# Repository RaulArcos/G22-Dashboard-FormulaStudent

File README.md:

# G22-Dashboard-FormulaStudent
DashBoard project with ATMEGA 328 using CAN BUS to communicate with Link G4+ Storm ECU.

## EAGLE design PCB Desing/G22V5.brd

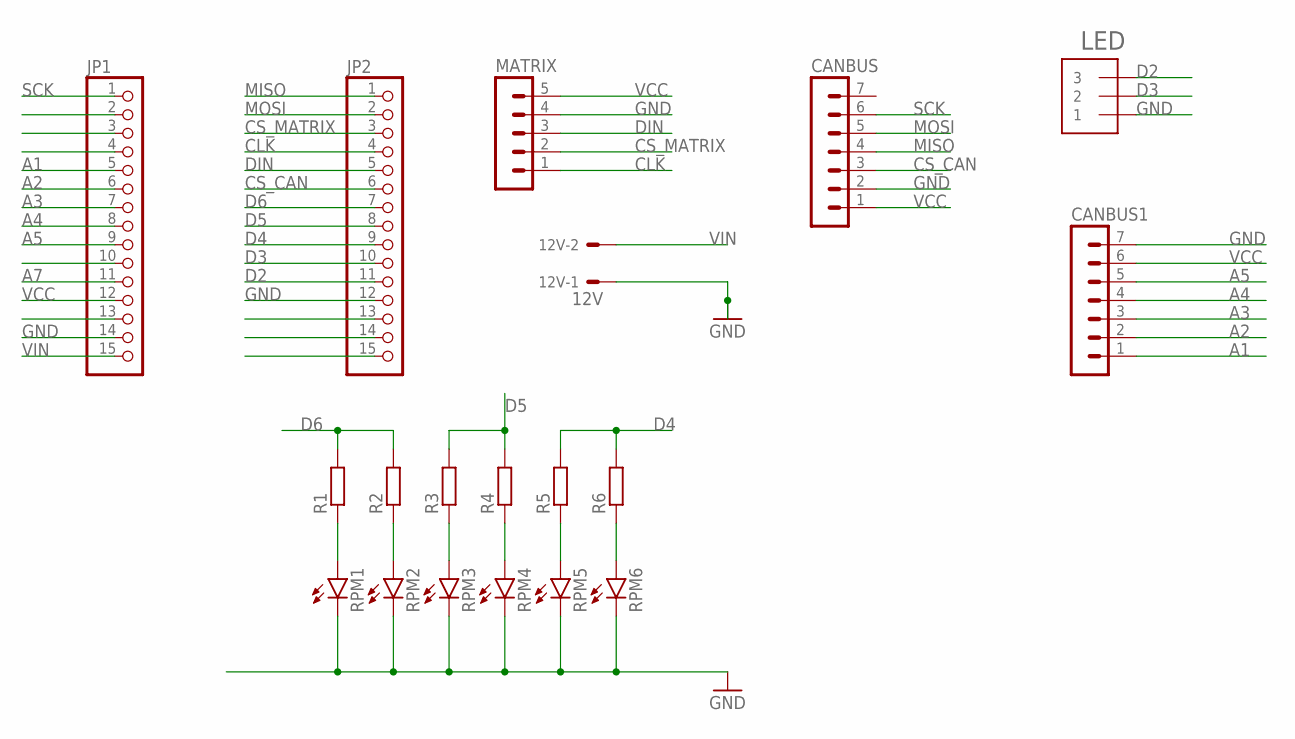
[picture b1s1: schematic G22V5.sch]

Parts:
12V: 12V; 22-23-2021
CANBUS, CANBUS1: MA07-1
JP1, JP2: PINHD-1X15; 1X15
LED: JST_ZH_3
MATRIX: MA05-1
R1, R2, R3, R4, R5, R6: R-EU_M0805; M0805
RPM1, RPM2, RPM3, RPM4, RPM5, RPM6: LED5MM

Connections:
A1: CANBUS1.1, JP1.5
A2: CANBUS1.2, JP1.6
A3: CANBUS1.3, JP1.7
A4: CANBUS1.4, JP1.8
A5: CANBUS1.5, JP1.9
A7: JP1.11
CLK: JP2.4, MATRIX.1
CS_CAN: CANBUS.3, JP2.6
CS_MATRIX: JP2.3, MATRIX.2
D2: JP2.11, LED.P$3 (3)
D3: JP2.10, LED.P$2 (2)
D4: JP2.9, R5.2, R6.2
D5: JP2.8, R3.2, R4.2
D6: JP2.7, R1.2, R2.2
DIN: JP2.5, MATRIX.3
GND: 12V.1, CANBUS.2, CANBUS1.7, JP1.14, JP2.12, LED.P$1 (1), MATRIX.4, RPM1.K (C), RPM2.K (C), RPM3.K (C), RPM4.K (C), RPM5.K (C), RPM6.K (C)
MISO: CANBUS.4, JP2.1
MOSI: CANBUS.5, JP2.2
unnamed: R1.1, RPM1.A
unnamed: R2.1, RPM2.A
unnamed: R3.1, RPM3.A
unnamed: R4.1, RPM4.A
unnamed: R5.1, RPM5.A
unnamed: R6.1, RPM6.A
SCK: CANBUS.6, JP1.1
VCC: CANBUS.1, CANBUS1.6, JP1.12, MATRIX.5
VIN: 12V.2, JP1.15

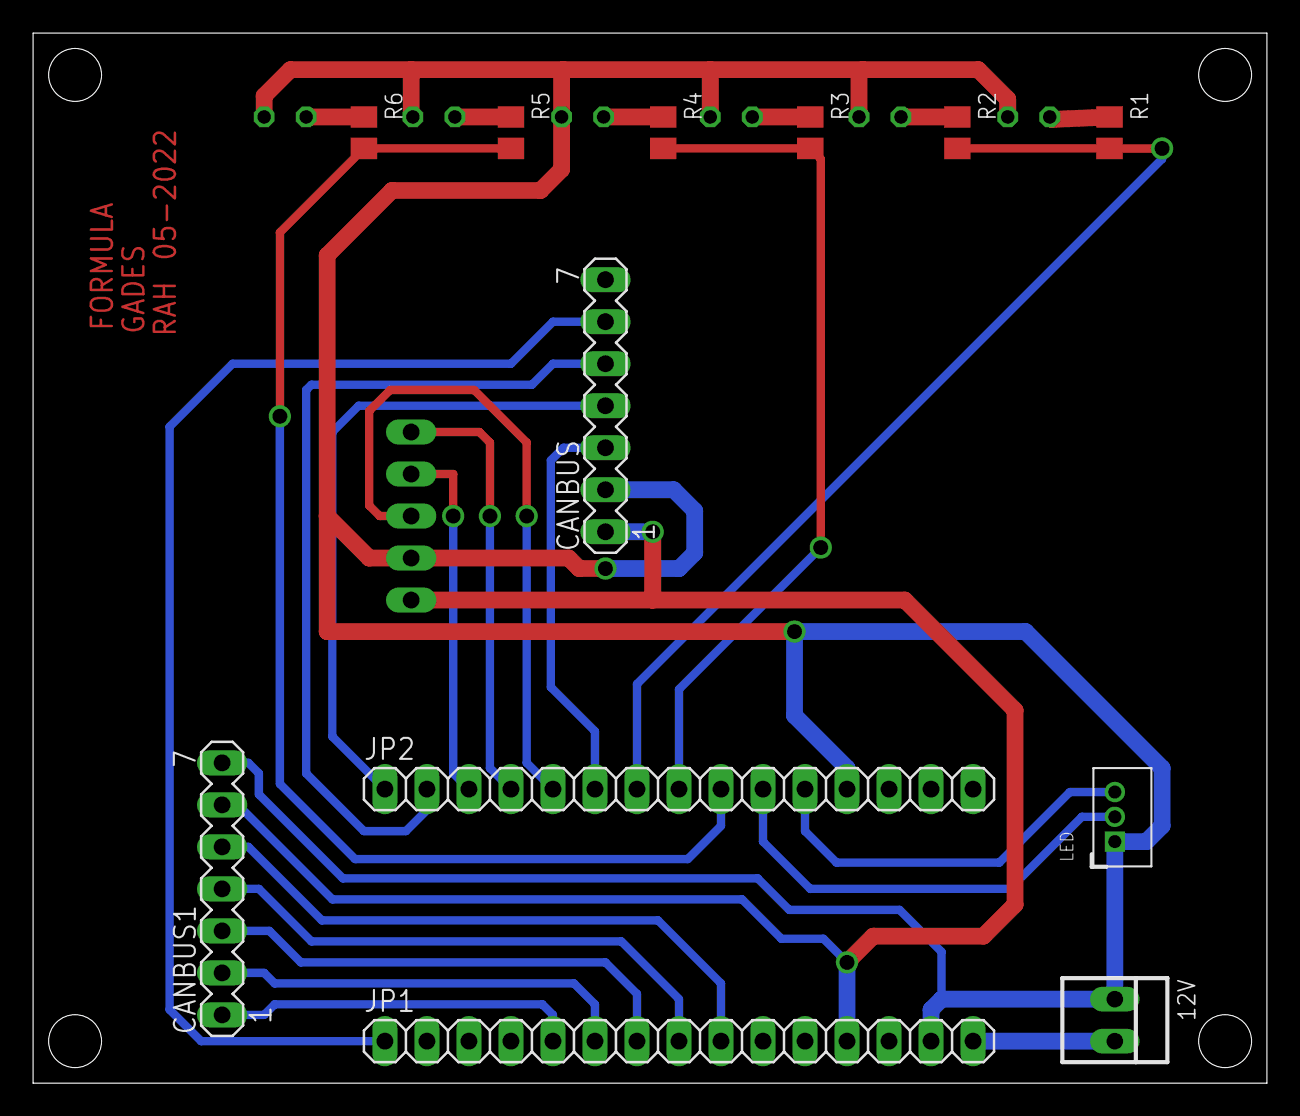
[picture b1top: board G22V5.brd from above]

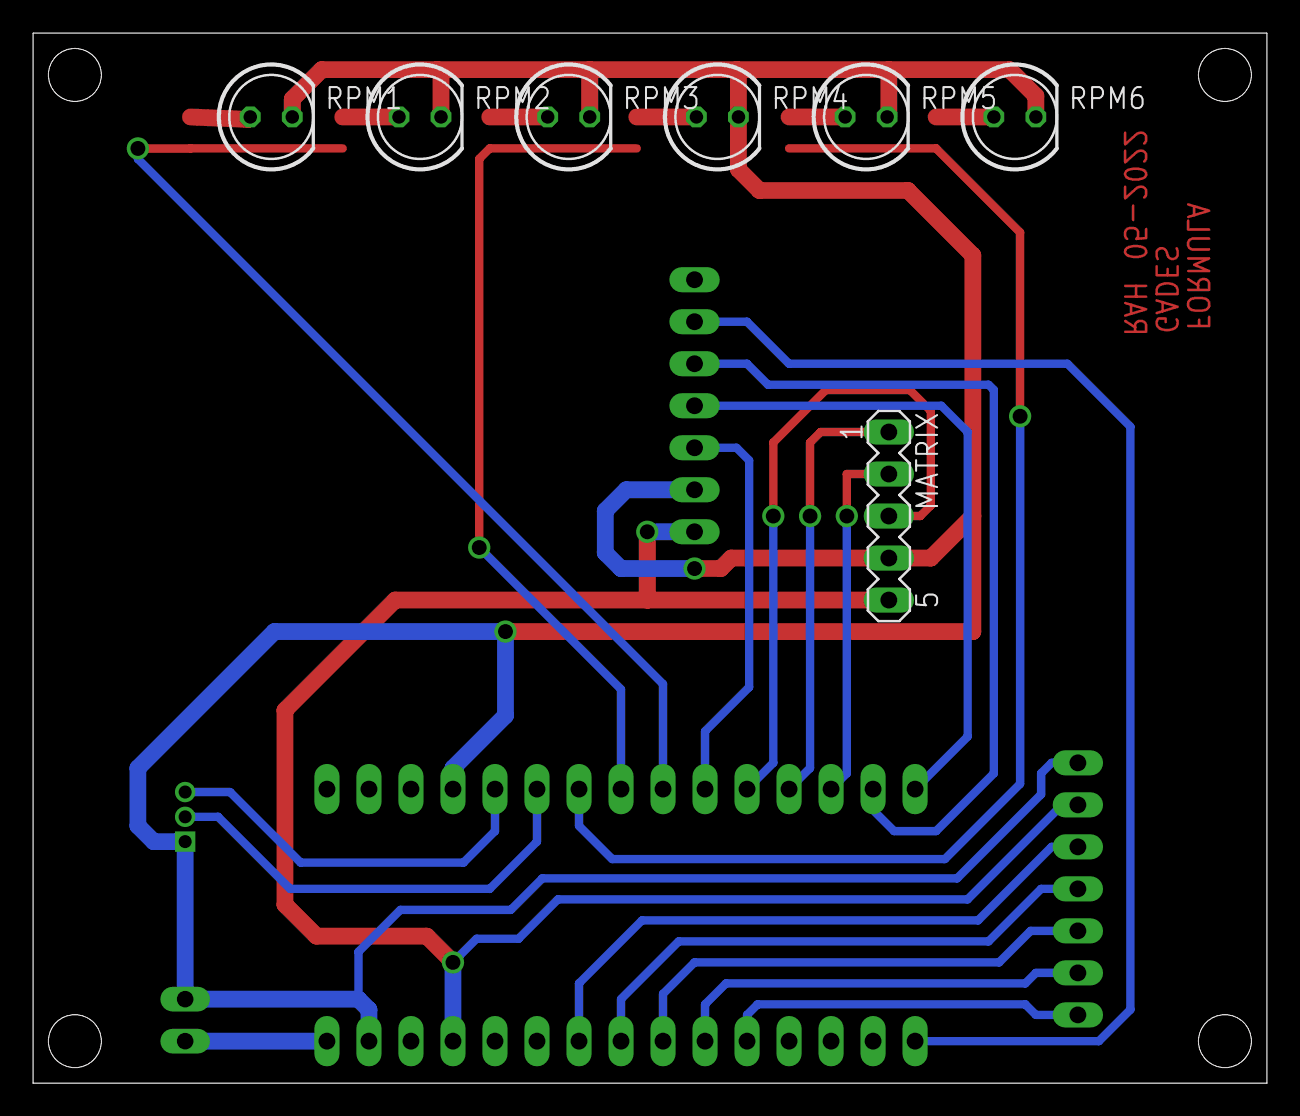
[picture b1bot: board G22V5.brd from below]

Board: 8 copper layers, 74.6 x 63.5 mm, 19 parts (7 on the bottom side), 26 nets.

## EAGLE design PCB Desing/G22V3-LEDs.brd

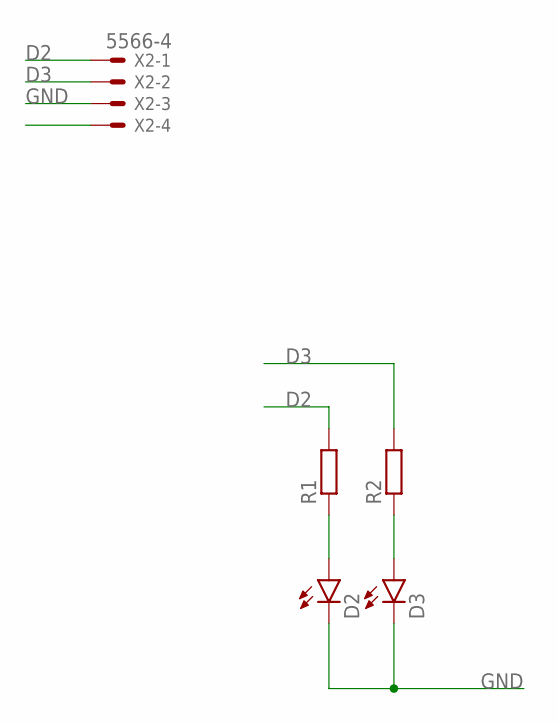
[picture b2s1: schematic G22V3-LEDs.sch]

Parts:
D2, D3: LED5MM
R1, R2: R-EU_0204/7; 0204/7
X2: 5566-4

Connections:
D2: R1.2, X2.1
D3: R2.2, X2.2
GND: D2.K (C), D3.K (C), X2.3
unnamed: D2.A, R1.1
unnamed: D3.A, R2.1

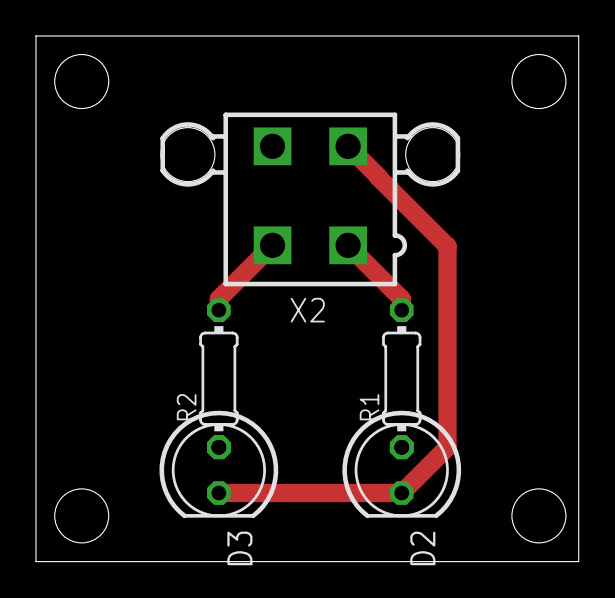
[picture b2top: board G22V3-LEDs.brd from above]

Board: 2 copper layers, 30.1 x 29.2 mm, 5 parts (0 on the bottom side), 5 nets.

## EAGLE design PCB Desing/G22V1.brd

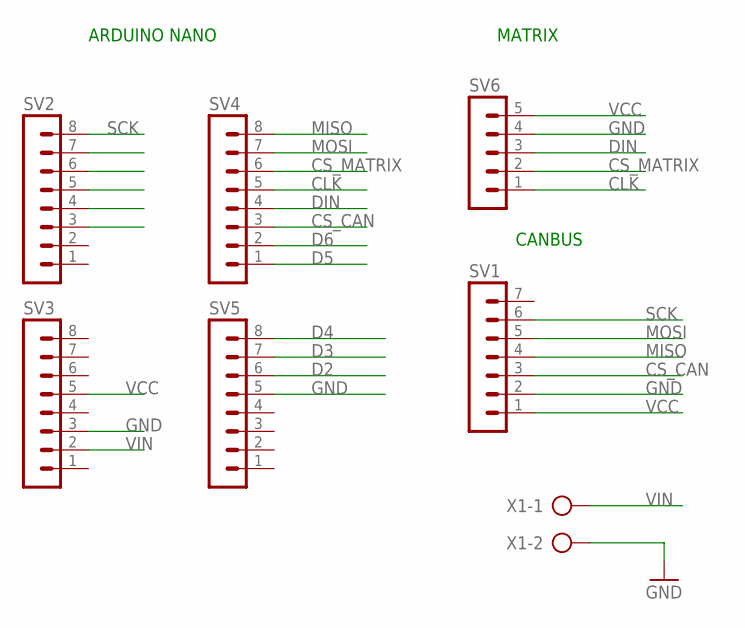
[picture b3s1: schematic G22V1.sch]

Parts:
SV1: MA07-1
SV2, SV3, SV4, SV5: MA08-1
SV6: MA05-1
X1: AK300/2

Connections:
CLK: SV4.5, SV6.1
CS_CAN: SV1.3, SV4.3
CS_MATRIX: SV4.6, SV6.2
D2: SV5.6
D3: SV5.7
D4: SV5.8
D5: SV4.1
D6: SV4.2
DIN: SV4.4, SV6.3
GND: SV1.2, SV3.3, SV5.5, SV6.4, X1.2
MISO: SV1.4, SV4.8
MOSI: SV1.5, SV4.7
SCK: SV1.6, SV2.8
VCC: SV1.1, SV3.5, SV6.5
VIN: SV3.2, X1.1

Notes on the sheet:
ARDUINO NANO
MATRIX
CANBUS

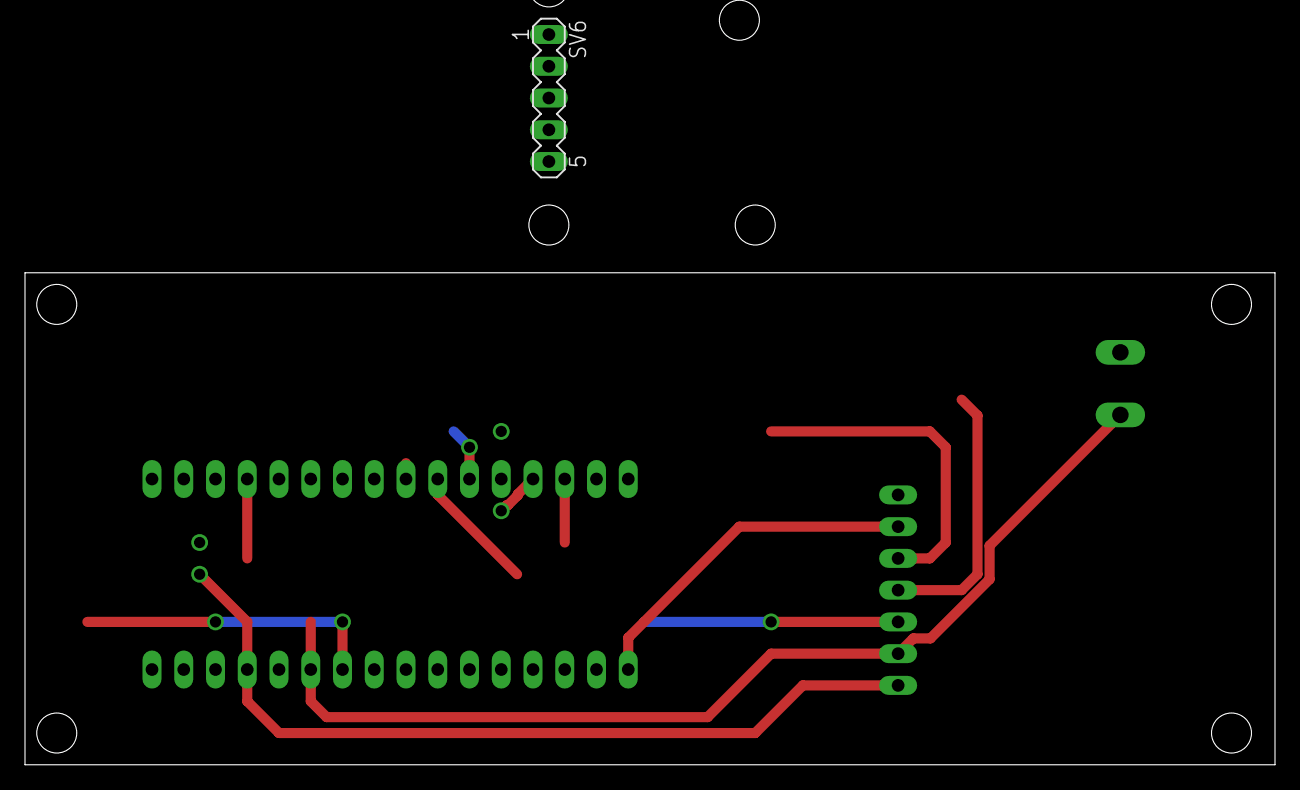
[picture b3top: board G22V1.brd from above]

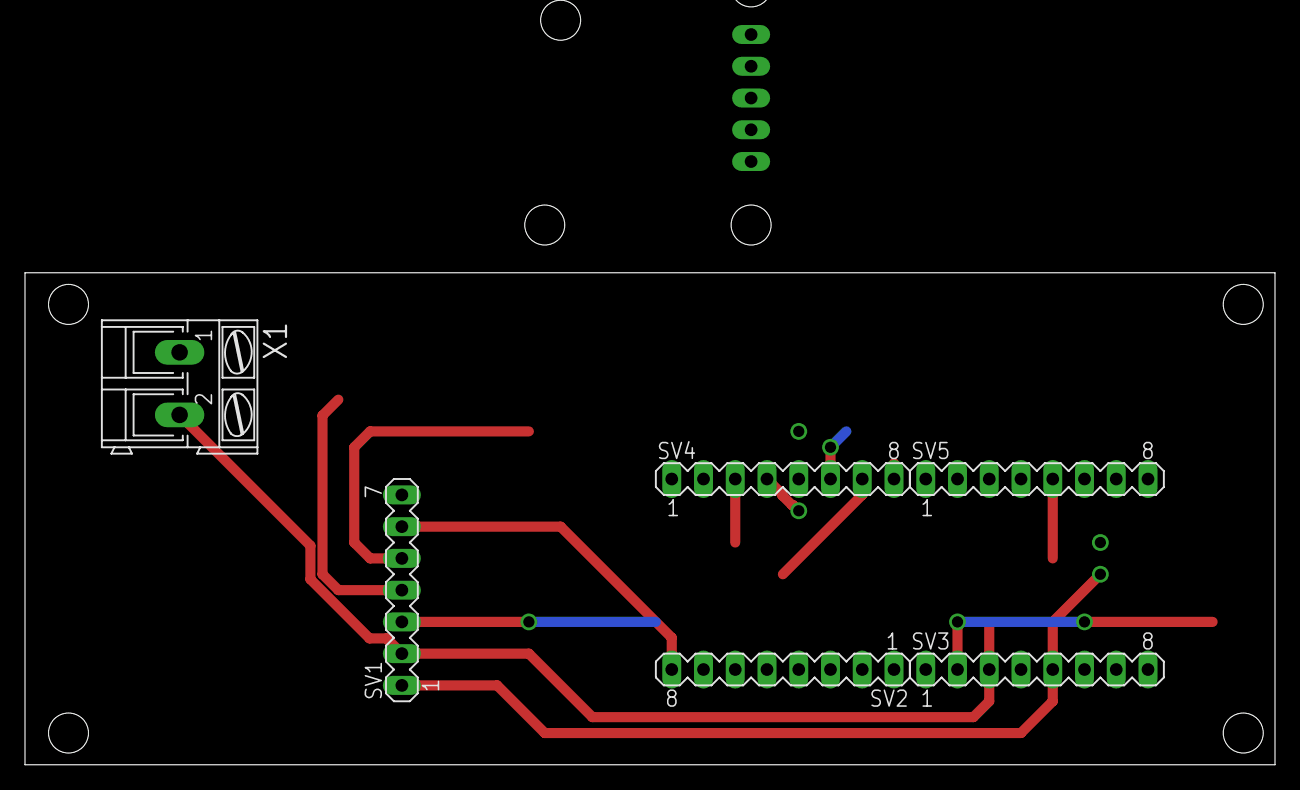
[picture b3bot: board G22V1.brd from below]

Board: 2 copper layers, 100.0 x 39.4 mm, 7 parts (6 on the bottom side), 10 nets.

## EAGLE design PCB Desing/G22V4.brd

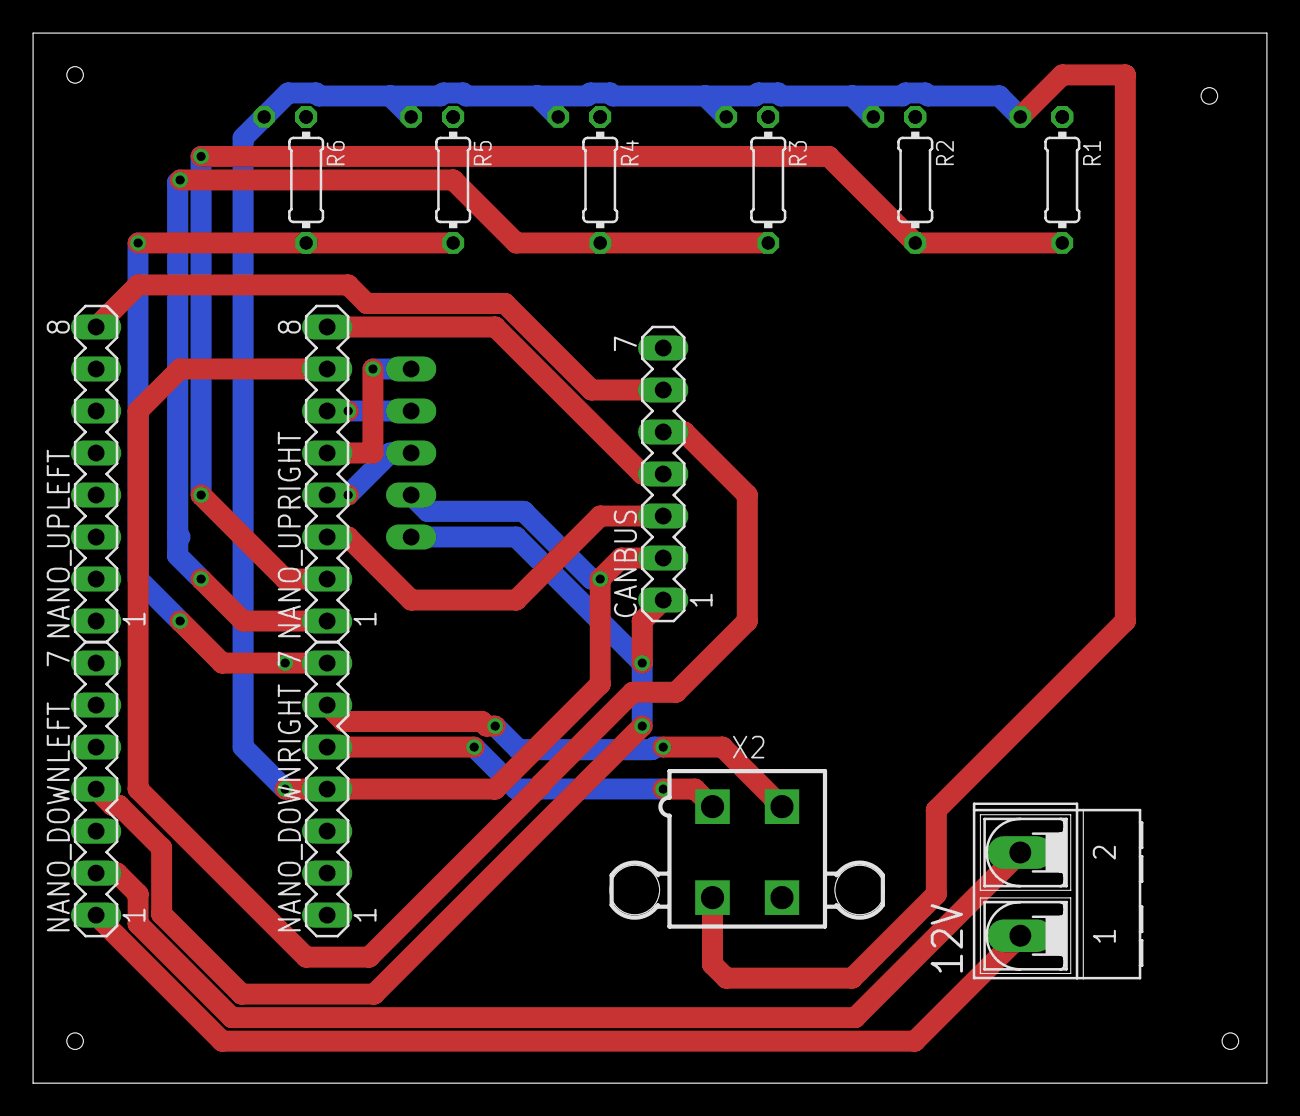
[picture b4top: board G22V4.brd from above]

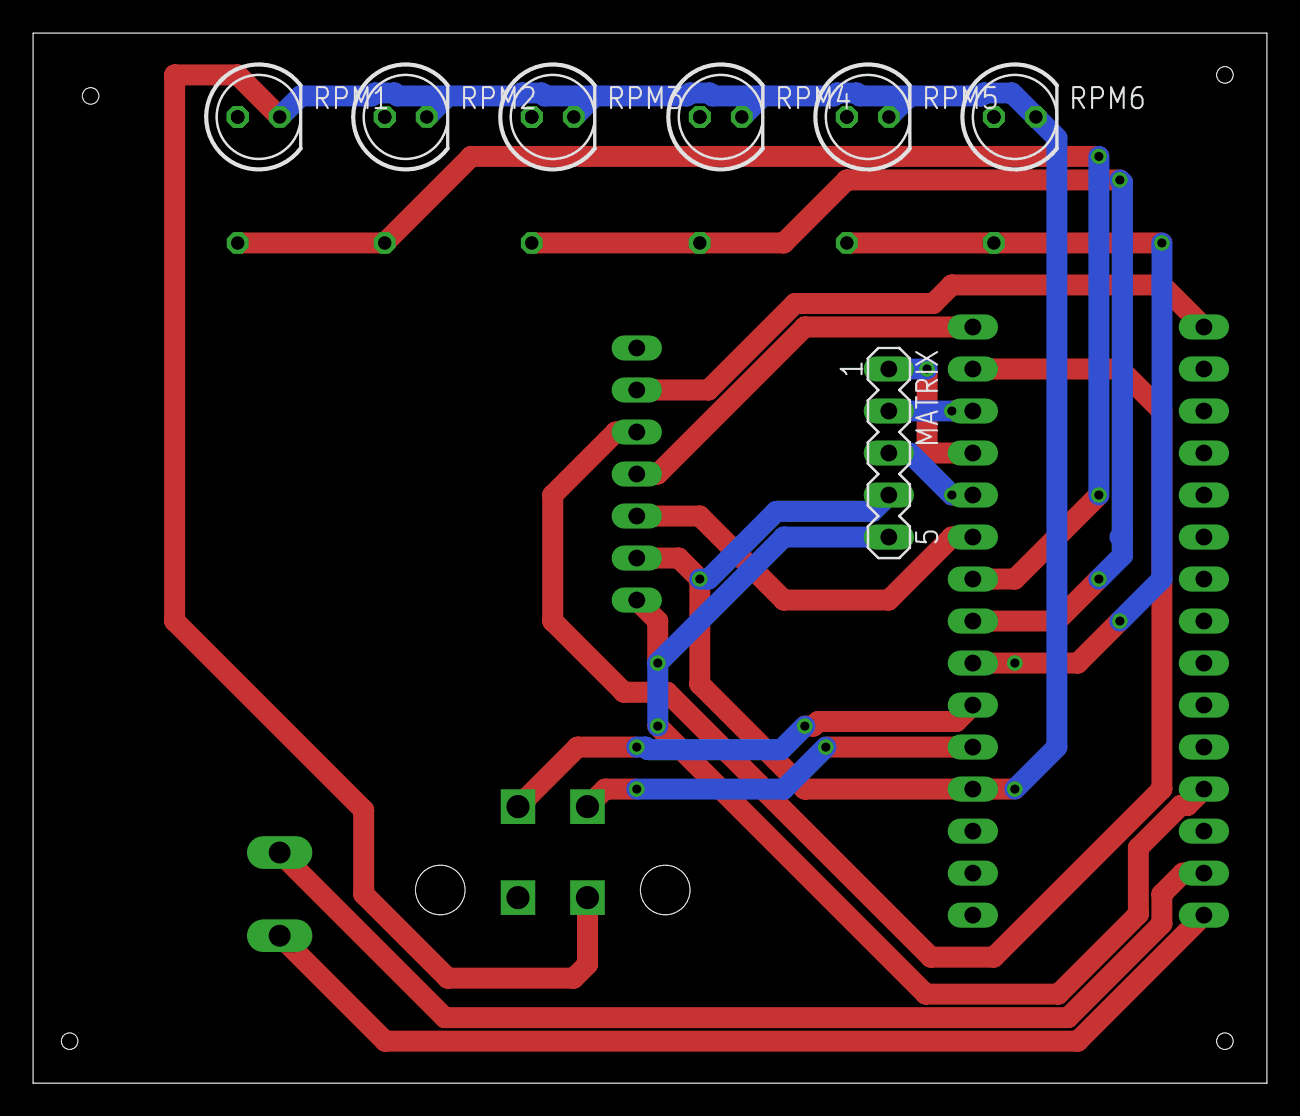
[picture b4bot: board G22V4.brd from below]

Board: 2 copper layers, 74.6 x 63.5 mm, 20 parts (7 on the bottom side), 21 nets.

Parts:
12V: AK500/2-H
CANBUS: MA07-1
MATRIX: MA05-1
NANO_DOWNLEFT: MA07-1
NANO_DOWNRIGHT: MA07-1
NANO_UPLEFT: MA08-1
NANO_UPRIGHT: MA08-1
R1, R2, R3, R4, R5, R6: 0204/7
RPM1, RPM2, RPM3, RPM4, RPM5, RPM6: LED5MM
X2: 5566-4

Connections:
CLK: MATRIX.1, NANO_UPRIGHT.5
CS_CAN: CANBUS.3, NANO_UPRIGHT.3
CS_MATRIX: MATRIX.2, NANO_UPRIGHT.6
D2: NANO_DOWNRIGHT.5, X2.1
D3: NANO_DOWNRIGHT.6, X2.2
D4: NANO_DOWNRIGHT.7, R5.2, R6.2
D5: NANO_UPRIGHT.1, R3.2, R4.2
D6: NANO_UPRIGHT.2, R1.2, R2.2
DIN: MATRIX.3, NANO_UPRIGHT.4
GND: 12V.2, CANBUS.2, MATRIX.4, NANO_DOWNLEFT.2, NANO_DOWNRIGHT.4, RPM1.K, RPM2.K, RPM3.K, RPM4.K, RPM5.K, RPM6.K, X2.3
MISO: CANBUS.4, NANO_UPRIGHT.8
MOSI: CANBUS.5, NANO_UPRIGHT.7
unnamed: R1.1, RPM1.A
unnamed: R2.1, RPM2.A
unnamed: R3.1, RPM3.A
unnamed: R4.1, RPM4.A
unnamed: R5.1, RPM5.A
unnamed: R6.1, RPM6.A
SCK: CANBUS.6, NANO_UPLEFT.8
VCC: CANBUS.1, MATRIX.5, NANO_DOWNLEFT.4
VIN: 12V.1, NANO_DOWNLEFT.1

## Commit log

2022-02-23 Añadido a Git
2022-03-08 Primera versión del código 2022
2022-03-30 Añadidas la PCB
2022-05-18 mas placas
2022-05-22 V4 donete
2022-06-06 he cambiao una cosa
2022-07-13 awdasd
2022-08-13 idk honestly
2022-10-22 Subidos los últimos diseños
